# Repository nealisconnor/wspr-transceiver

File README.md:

# WSPR Transceiver — ELEC3607 Assignment 1

Group assignment modifying the WSPR-SDR platform to add a transmit path and redesigning the PCB as a full transceiver.

## Overview

**Part A — Software Transmitter**  
Drives the Si5351's CLK2 output to generate a WSPR-encoded signal, looped back to the receiver input at RF. A C program encodes callsign, Maidenhead locator, and power level into the WSPR protocol and controls CLK2 via I²C.

**Part B — PCB Redesign**  
Modifies the WSPR-SDR KiCad layout to add a 0.1 W PA stage and GPIO-controlled T/R switch sharing the existing bandpass filter. Components from element14 AU. JLCPCB 2-layer spec.

## Repository Structure

```
wspr-transceiver/
├── software/               # Part A — C transmitter
│   ├── wspr_transmit.c
│   ├── wspr_encode.c/h
│   └── Makefile
├── hardware/               # Part B — KiCad project
│   ├── bbb/
│       ├── bbb.kicad_pro     # Kicad project
│       ├── bbb.kicad_sch     # schematic
│       ├── bbb.kicad_pcb     # pcb layout
│       ├── Kicad_libs        # contains symbols and footprints of new components
│       ├── *.gbr             # Gerbers
│       ├── *.drl             # drill files
│       ├── *.net             # netlist
│       └── *.csv             # BOM
├── report/                 # IEEE-format PDF report
└── README.md
```

## Part A — Build & Run

```bash
cd software && make
./wspr_transmit VK2AAX QF56 3
# args: <callsign> <grid_locator> <power_dBm>
```

Targets `/dev/i2c-3`, address `0x60` (Si5351). Fit loopback jumper before running.

## Part B — KiCad

Open `hardware/bbb/bbb.kicad_pro` in KiCad 8.x. Upstream reference: [phwl/elec3607-lab pcb_2026](https://github.com/phwl/elec3607-lab/tree/main/pcb_2026).

## Hardware Target

- BeagleBone / PetaLinux
- Si5351: CLK0/CLK1 → Tayloe detector, CLK2 → TX
- I²C: `/dev/i2c-3`, `0x60`

## Team

University of Sydney — ELEC3607, Semester 1 2026.

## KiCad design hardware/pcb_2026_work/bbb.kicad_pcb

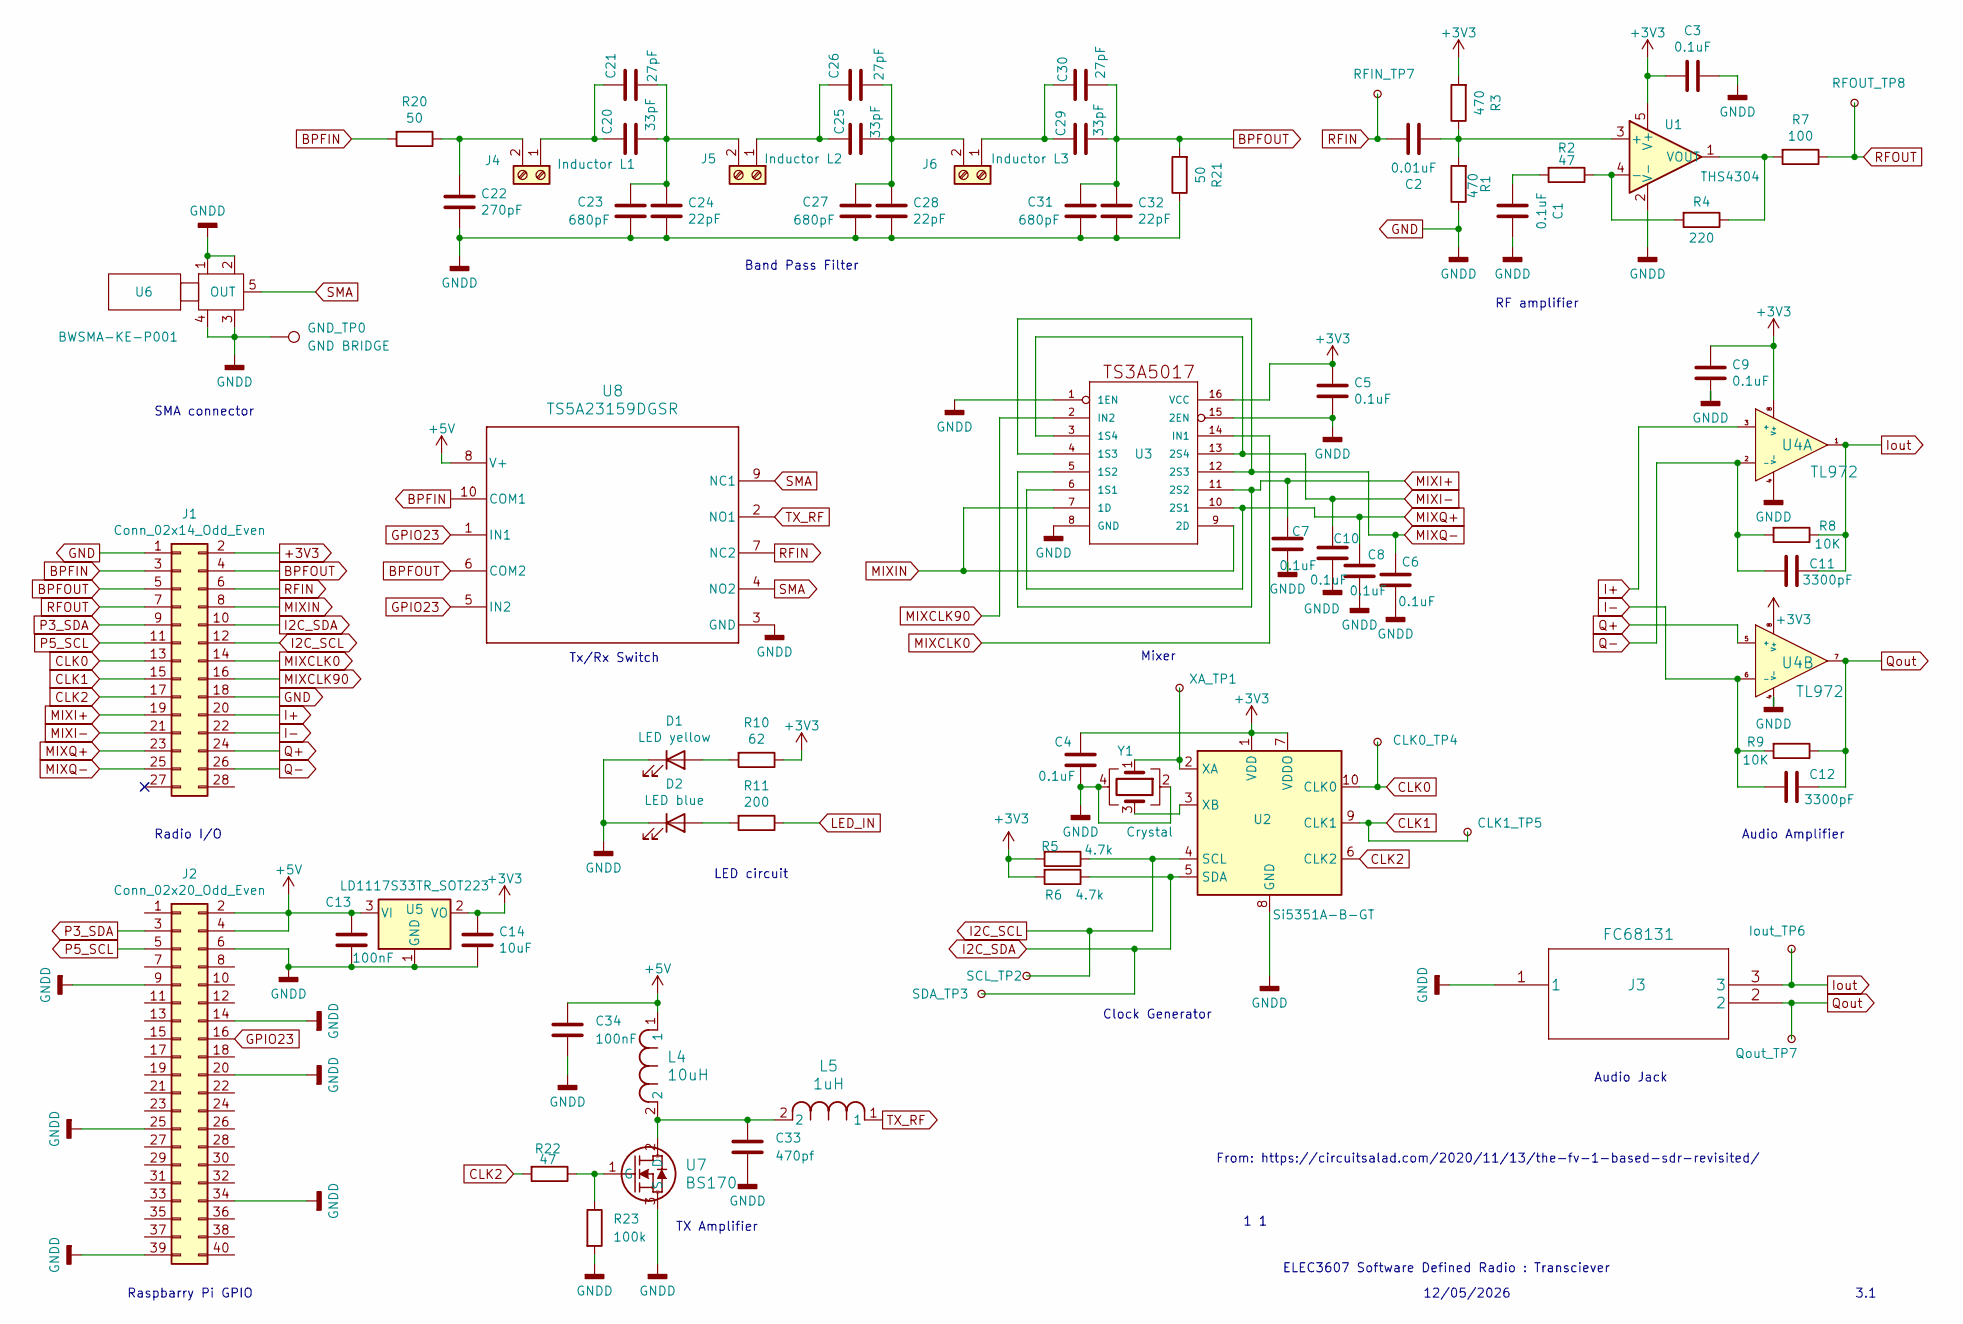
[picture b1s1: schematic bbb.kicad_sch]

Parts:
C1, C3, C4, C5, C6, C7, C8, C9, C10: 0.1uF; C_0805_2012Metric
C2: 0.01uF; C_0805_2012Metric
C11, C12: 3300pF; C_0805_2012Metric
C13, C34: 100nF; C_0805_2012Metric
C14: 10uF; C_0805_2012Metric
C20, C25, C29: 33pF; C_0805_2012Metric
C21, C26, C30: 27pF; C_0805_2012Metric
C22: 270pF; C_0805_2012Metric
C23, C27, C31: 680pF; C_0805_2012Metric
C24, C28, C32: 22pF; C_0805_2012Metric
C33: 470pf; C_0805_2012Metric
CLK0_TP4, CLK1_TP5: TestPoint_Small; TestPoint_Keystone_5000-5004_Miniature
D1: LED yellow; D_0603_1608Metric
D2: LED blue; D_0603_1608Metric
GND_TP0: GND BRIDGE; TestPoint_Bridge_Pitch7.62mm_Drill1.3mm
Iout_TP6: TestPoint_Small; TestPoint_Keystone_5000-5004_Miniature
J1: Conn_02x14_Odd_Even; PinHeader_2x14_P2.54mm_Vertical
J2: Conn_02x20_Odd_Even; PinHeader_2x20_P2.54mm_Vertical
J3: FC68131
J4: Inductor L1; TerminalBlock_Phoenix_MPT-0,5-2-2.54_1x02_P2.54mm_Horizontal
J5: Inductor L2; TerminalBlock_Phoenix_MPT-0,5-2-2.54_1x02_P2.54mm_Horizontal
J6: Inductor L3; TerminalBlock_Phoenix_MPT-0,5-2-2.54_1x02_P2.54mm_Horizontal
L4: 10uH; IND_2012_TDK
L5: 1uH; IND_1608_TDK
Qout_TP7: TestPoint_Small; TestPoint_Keystone_5000-5004_Miniature
R1, R3: 470; R_0805_2012Metric
R2, R22: 47; R_0805_2012Metric
R4: 220; R_0805_2012Metric
R5, R6: 4.7k; R_0805_2012Metric
R7: 100; R_0805_2012Metric
R8, R9: 10K; R_0805_2012Metric
R10: 62; R_0805_2012Metric
R11: 200; R_0805_2012Metric
R20, R21: 50; R_0805_2012Metric
R23: 100k; R_0805_2012Metric
RFIN_TP7: TestPoint_Small; TestPoint_Keystone_5000-5004_Miniature
RFOUT_TP8: TestPoint_Small; TestPoint_Keystone_5000-5004_Miniature
SCL_TP2: TestPoint_Small; TestPoint_Keystone_5000-5004_Miniature
SDA_TP3: TestPoint_Small; TestPoint_Keystone_5000-5004_Miniature
U1: THS4304; SOT-23-5
U2: Si5351A-B-GT; MSOP-10_3x3mm_P0.5mm
U3: TS3A5017; SOIC-16_3.9x9.9mm_P1.27mm
U4: TL972; SOIC-8-1EP_3.9x4.9mm_P1.27mm_EP2.29x3mm
U5: LD1117S33TR_SOT223; SOT-223-3_TabPin2
U6: BWSMA-KE-P001
U7: BS170; TO_SA06_ONS
U8: TS5A23159DGSR; DGS0010A_N
XA_TP1: TestPoint_Small; TestPoint_Keystone_5000-5004_Miniature
Y1: Crystal; Crystal_SMD_TXC_7M-4Pin_3.2x2.5mm

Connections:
+3V3: C3.2, C4.1, C5.1, C9.1, C14.1, J1.2, R3.2, R5.2, R6.2, R10.1, U1.5 (V+), U2.1 (VDD), U2.7 (VDDO), U3.16 (VCC), U4.8 (V+), U5.2 (VO)
+5V: C13.1, C34.1, J2.2, J2.4, L4.1, U5.3 (VI), U8.8 (V+)
BPFIN: J1.3, R20.2, U8.10 (COM1)
BPFOUT: C29.2, C30.2, C31.1, C32.1, J1.4, J1.5, R21.2, U8.6 (COM2)
CLK0: CLK0_TP4.1 (1_1), J1.13, U2.10 (CLK0)
CLK1: CLK1_TP5.1 (1_1), J1.15, U2.9 (CLK1)
CLK2: J1.17, R22.2, U2.6 (CLK2)
GND: C1.1, C3.1, C4.2, C5.2, C6.2, C7.2, C8.2, C9.2, C10.2, C13.2, C14.2, C22.2, C23.2, C24.2, C27.2, C28.2, C31.2, C32.2, C33.2, C34.2, D1.1 (K), D2.1 (K), GND_TP0.1 (1_1), J1.1, J1.18, J2.6, J2.9, J2.14, J2.20, J2.25, J2.34, J2.39, J3.1, R1.1, R21.1, R23.2, U1.2 (V-), U2.8 (GND), U3.1 (1EN), U3.8 (GND), U3.15 (2EN), U4.4 (V-), U5.1 (GND), U6.1, U6.2, U6.3, U6.4, U7.3 (S), U8.3 (GND), Y1.2, Y1.4
GPIO23: J2.16, U8.1 (IN1), U8.5 (IN2)
I2C_SCL: J1.12, R5.1, SCL_TP2.1 (1_1), U2.4 (SCL)
I2C_SDA: J1.10, R6.1, SDA_TP3.1 (1_1), U2.5 (SDA)
I+: J1.20, U4.3 (+)
I-: C12.2, J1.22, R9.2, U4.6 (-)
Iout: C11.1, Iout_TP6.1 (1_1), J3.3, R8.1, U4.1
LED_IN: R11.1
MIXCLK0: J1.14, U3.14 (IN1)
MIXCLK90: J1.16, U3.2 (IN2)
MIXI+: C7.1, J1.19, U3.5 (1S2), U3.11 (2S2)
MIXI-: C10.1, J1.21, U3.3 (1S4), U3.13 (2S4)
MIXIN: J1.8, U3.7 (1D), U3.9 (2D)
MIXQ+: C8.1, J1.23, U3.6 (1S1), U3.10 (2S1)
MIXQ-: C6.1, J1.25, U3.4 (1S3), U3.12 (2S3)
unnamed: C1.2, R2.2
unnamed: D1.2 (A), R10.2
unnamed: D2.2 (A), R11.2
unnamed: C20.1, C21.1, J4.1
unnamed: C22.1, J4.2, R20.1
unnamed: C25.1, C26.1, J5.1
unnamed: C20.2, C21.2, C23.1, C24.1, J5.2
unnamed: C29.1, C30.1, J6.1
unnamed: C25.2, C26.2, C27.1, C28.1, J6.2
unnamed: C2.2, R1.2, R3.1, U1.3 (+)
unnamed: R2.1, R4.2, U1.4 (-)
unnamed: R4.1, R7.2, U1.1 (VOUT)
unnamed: U2.2 (XA), XA_TP1.1 (1_1), Y1.1
unnamed: U2.3 (XB), Y1.3
unnamed: C33.1, L4.2, L5.2, U7.2 (D)
unnamed: R22.1, R23.1, U7.1 (G)
P3_SDA: J1.9, J2.3
P5_SCL: J1.11, J2.5
Q+: J1.24, U4.5 (+)
Q-: C11.2, J1.26, R8.2, U4.2 (-)
Qout: C12.1, J3.2, Qout_TP7.1 (1_1), R9.1, U4.7
RFIN: C2.1, J1.6, RFIN_TP7.1 (1_1), U8.7 (NC2)
RFOUT: J1.7, R7.1, RFOUT_TP8.1 (1_1)
SMA: U6.5 (OUT_5), U8.4 (NO2), U8.9 (NC1)
TX_RF: L5.1, U8.2 (NO1)

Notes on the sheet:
Audio Amplifier
TX Amplifier
Tx/Rx Switch
LED circuit
SMA connector
Raspbarry Pi GPIO
Audio Jack
12/05/2026
Radio I/O
Clock Generator
ELEC3607 Software Defined Radio : Transciever
3.1
From: https://circuitsalad.com/2020/11/13/the-fv-1-based-sdr-revisited/
Band Pass Filter
Mixer
1 1
RF amplifier

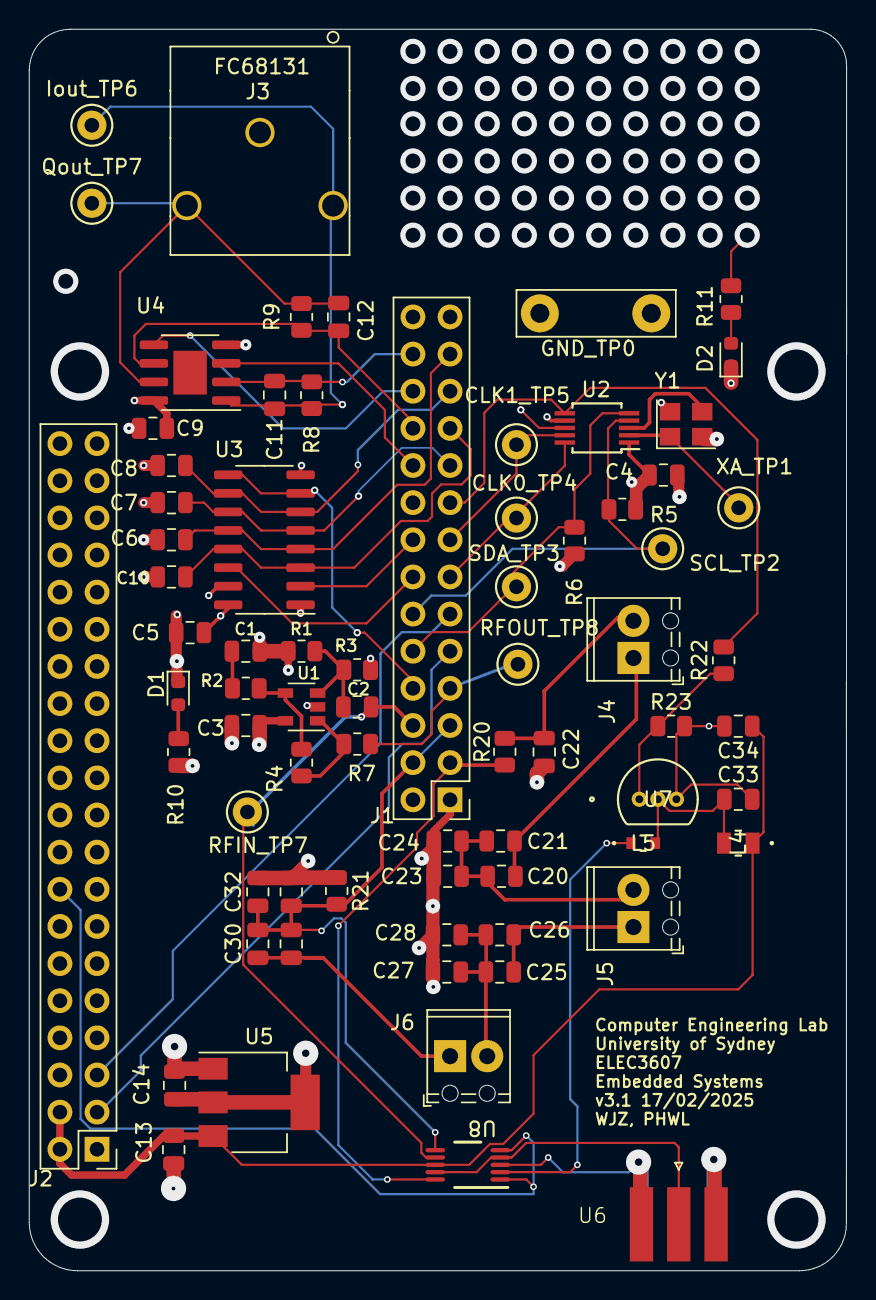
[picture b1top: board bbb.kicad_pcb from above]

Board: 4 copper layers, 55.9 x 84.9 mm, 73 parts (0 on the bottom side), 46 nets.

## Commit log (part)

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2026-05-10 Add .gitignore to exclude build artifacts and backups
2026-05-10 Enhance README with project details and instructions
    Expanded the README to provide a detailed overview of the WSPR Transceiver project, including software and hardware components, repository structure, build instructions, and team information.
2026-05-10 added encoding file converted from python to C
2026-05-10 Test related files will be here
    Added test on how to try out the wav gen and then k9an in the lab using the old wsprd file in the lab.
    All files are not in here yet, what is needed is basically all the headers and other stuff that allows wsprd.c to run (in lab 5)
    and the encoder in the sofware folder, for now I put the transmit file here can move it out later.
2026-05-11 Update README.md for clarity and corrections
    Corrected the I²C bus reference and clarified existing lab files.
2026-05-12 KiCad Additions
    Adding KiCad files
2026-05-12 updated schematic and pcb editor files
2026-05-12 Cleaning Up for Branch
    Cleaning stuff
2026-05-13 gerber files
2026-05-15 Adding PartA files to software folder
    moving from report to overall software section
2026-05-16 added group member names. Added remaining partB info. Adjusted formatting
2026-05-16 fixed page overflow
2026-05-16 PartA code references
    Added exerpts of each code screenshot (short forms of important lines in a function, but not the entire code.)
2026-05-16 PDF version of A1 with code snippet
    Pdf version of the recent latex push that has the code snippet mentioned in the report
    a few things to note...
    I did not name the code snippets as figures, if we want can do this
    I believe appendices don't count for report page
2026-05-17 final schematic and layout filles
    Upload these for part B
2026-05-17 uploaded BOM
2026-05-17 Delete hardware/pcb_2026_work directory
    old working files, not required anymore
2026-05-17 updated hardware directory tree
2026-05-17 Fix formatting in README.md for hardware section
2026-05-17 Reorganise report/: consolidate into PartB/ working structure
    - Move active .tex to report/PartB/ with fixed \graphicspath{{../}{./}}
    - Consolidate all Part B figures into PartB/
    - Flatten Part A figures to report/ root (resolved by ../ path)
    - Remove build artifacts, duplicate images, and old root-level .tex
    - Add .claude/ and .history to .gitignore
2026-05-17 Flatten report/ structure — single directory, all figures at root
2026-05-17 Fix LaTeX formatting consistency in report
    - Remove abstract and IEEEkeywords
    - Convert Part B display math ($$) to equation environments
    - Replace \medskip with proper paragraph breaks
    - Fix units: uH -> \mu\text{H}, 100K\Omega -> 100\,\text{k}\Omega
    - Clean up 'where \begin{equation}' inline placement
    - Fix Element14 bibitem (backtick -> correct quote, add URL)
2026-05-17 final changes

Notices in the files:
parts and their libraries:
Copyright 2021 Accelerated Designs. All rights reserved.
